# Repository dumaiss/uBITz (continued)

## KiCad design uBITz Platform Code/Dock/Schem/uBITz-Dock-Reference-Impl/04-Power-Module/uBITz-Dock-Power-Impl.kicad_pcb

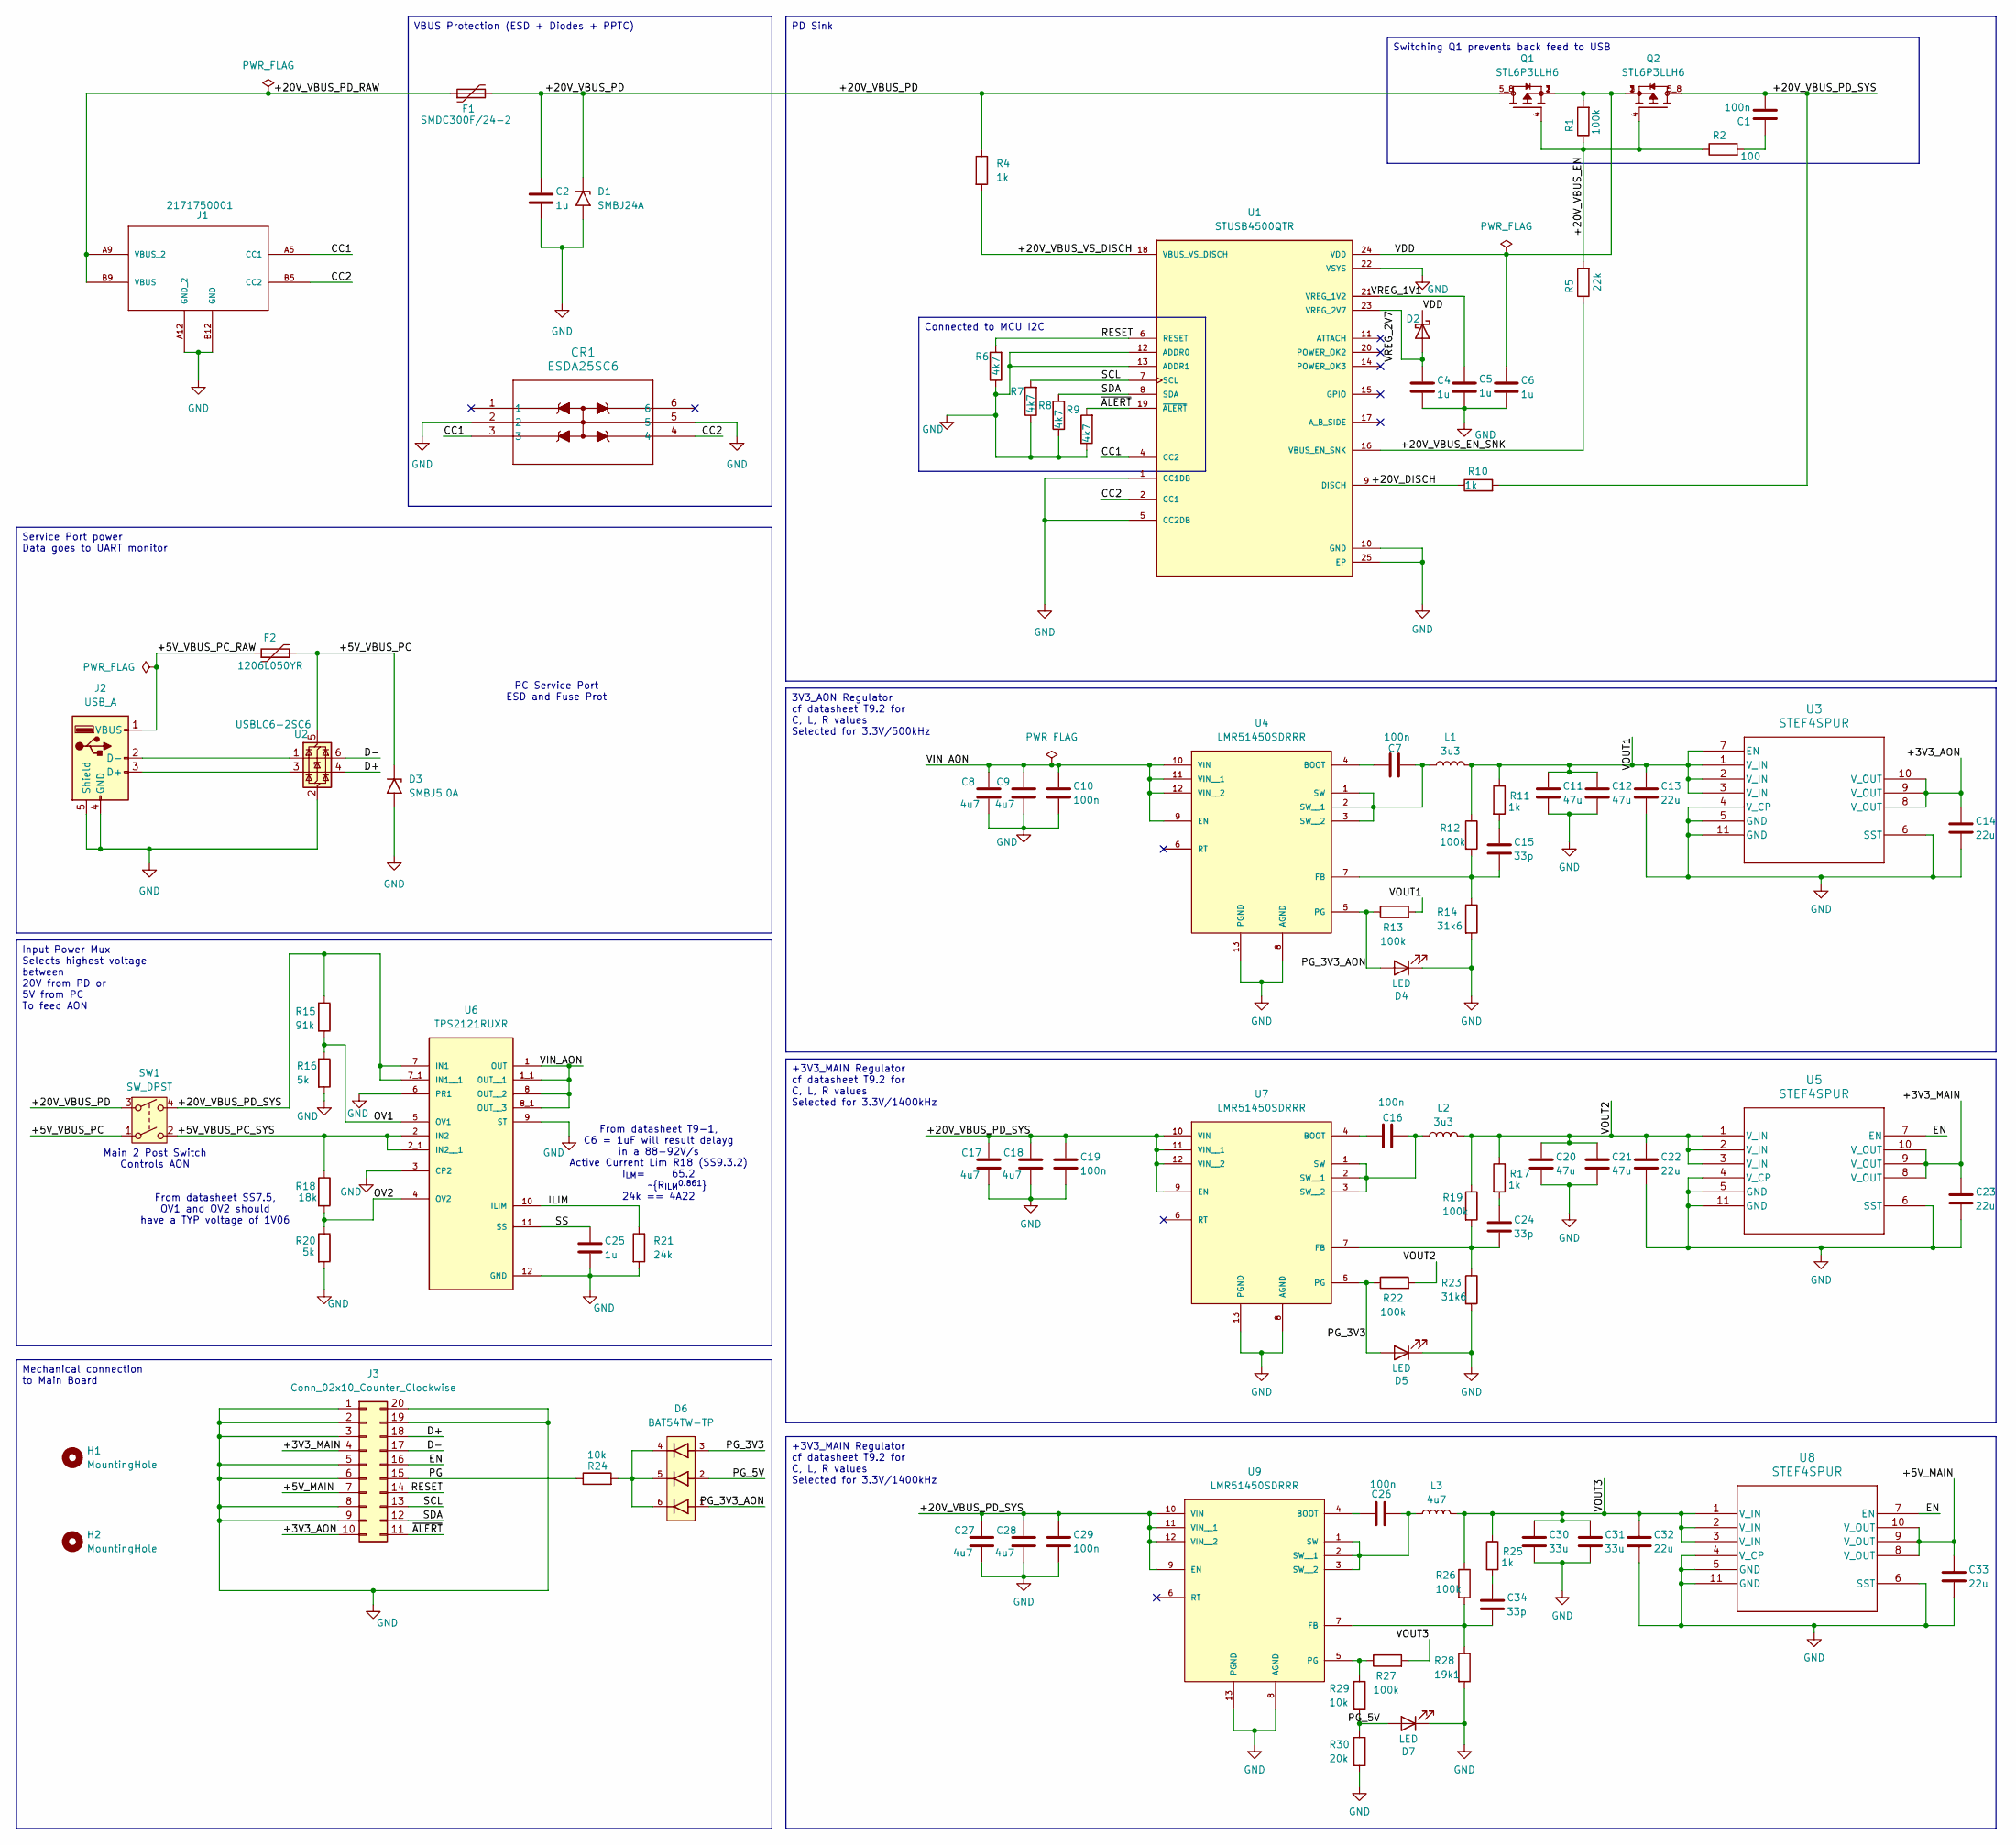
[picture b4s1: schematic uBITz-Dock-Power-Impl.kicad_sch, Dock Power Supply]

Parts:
C1, C7, C10, C16, C19, C26, C29: 100n; C_0603_1608Metric
C2: 1u; C_0402_1005Metric
C4, C5, C6, C25: 1u; C_0603_1608Metric
C8, C9, C17, C18, C27, C28: 4u7; C_0603_1608Metric
C11, C12, C20, C21: 47u; C_0603_1608Metric
C13, C14, C22, C23, C32, C33: 22u; C_0603_1608Metric
C15, C24, C34: 33p; C_0603_1608Metric
C30, C31: 33u; C_0603_1608Metric
CR1: ESDA25SC6; SOT23-6L_STM
D1: SMBJ24A; D_SMA_Handsoldering
D2: D_Schottky; D_SOD-323_HandSoldering
D3: SMBJ5.0A; D_SMB_Handsoldering
D4, D5, D7: LED; LED_0603_1608Metric
D6: BAT54TW-TP; SOP65P222X120-6N; PARTREV Rev.3
F1: SMDC300F/24-2; Fuse_2920_7451Metric_Pad2.10x5.45mm_HandSolder
F2: 1206L050YR; Fuse_1206_3216Metric
H1, H2: MountingHole; MountingHole_2.5mm
J1: 2171750001; 2171750001_MOL; MANUFACTURER_PART_NUMBER 2171750001
J2: USB_A; USB_A_Molex_67643_Horizontal
J3: Conn_02x10_Counter_Clockwise; PinHeader_2x10_P2.54mm_Vertical
L1, L2: 3u3; L_Bourns_SRP7028A_7.3x6.6mm; Part SRP7028A-3R3M
L3: 4u7; L_Bourns_SRP7028A_7.3x6.6mm
Q1, Q2: STL6P3LLH6; TRANS_STL6P3LLH6; PARTREV 4
R1, R12, R13, R19, R22, R26, R27: 100k; R_0603_1608Metric
R2: 100; R_0603_1608Metric
R4, R10, R11, R17, R25: 1k; R_0603_1608Metric
R5: 22k; R_0603_1608Metric
R6, R7, R8, R9: 4k7; R_0603_1608Metric
R14, R23: 31k6; R_0603_1608Metric
R15: 91k; R_0603_1608Metric
R16, R20: 5k; R_0603_1608Metric
R18: 18k; R_0603_1608Metric
R21: 24k; D_0603_1608Metric
R24, R29: 10k; R_0603_1608Metric
R28: 19k1; R_0603_1608Metric
R30: 20k; R_0603_1608Metric
SW1: SW_DPST; Molex_KK-254_AE-6410-04A_1x04_P2.54mm_Vertical; Part# 0022272041
U1: STUSB4500QTR; QFN50P400X400X90-25N; PARTREV 2
U2: USBLC6-2SC6; SOT-23-6
U3, U5, U8: STEF4SPUR; DFN_4SPUR_STM-L
U4, U7, U9: LMR51450SDRRR; CONV_LMR51450SDRRR; PARTREV December 2022
U6: TPS2121RUXR; IC_TPS2121RUXR

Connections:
/+3V3_AON: C14.1, J3.10, U3.8 (V_OUT), U3.9 (V_OUT), U3.10 (V_OUT)
/+3V3_MAIN: C23.1, J3.4, U5.8 (V_OUT), U5.9 (V_OUT), U5.10 (V_OUT)
/+5V_MAIN: C33.1, J3.7, U8.8 (V_OUT), U8.9 (V_OUT), U8.10 (V_OUT)
/+5V_VBUS_PC: D3.1 (A1), F2.2, SW1.1, U2.5 (VBUS)
/+5V_VBUS_PC_RAW: F2.1, J2.1 (VBUS)
/+5V_VBUS_PC_SYS: R18.1, SW1.2, U6.2 (IN2), U6.2_1 (IN2__1)
/+20V_DISCH: R10.1, U1.9 (DISCH)
/+20V_VBUS_EN: Q1.4, Q2.4, R1.1, R2.1, R5.2
/+20V_VBUS_EN_SNK: R5.1, U1.16 (VBUS_EN_SNK)
/+20V_VBUS_PD: C2.1, D1.1 (A1), F1.2, Q1.5_8, R4.1, SW1.3
/+20V_VBUS_PD_RAW: F1.1, J1.A9 (VBUS_2), J1.B9 (VBUS)
/+20V_VBUS_PD_SYS: C1.2, C17.1, C18.1, C19.1, C27.1, C28.1, C29.1, Q2.5_8, R10.2, R15.1, SW1.4, U6.7 (IN1), U6.7_1 (IN1__1), U7.9 (EN), U7.10 (VIN), U7.11 (VIN__1), U7.12 (VIN__2), U9.9 (EN), U9.10 (VIN), U9.11 (VIN__1), U9.12 (VIN__2)
/+20V_VBUS_VS_DISCH: R4.2, U1.18 (VBUS_VS_DISCH)
/CC1: CR1.3, J1.A5 (CC1), U1.4 (CC2)
/CC2: CR1.4, J1.B5 (CC2), U1.2 (CC1)
/D+: J3.18, U2.4 (I/O2)
/D-: J3.17, U2.6 (I/O1)
/EN: J3.16, U5.7 (EN), U8.7 (EN)
/ILIM: R21.1, U6.10 (ILIM)
/OV1: R15.2, R16.1, U6.5 (OV1)
/OV2: R18.2, R20.1, U6.4 (OV2)
/PG: J3.15, R24.1
/PG_3V3: D5.2 (A), D6.3, R22.1, U7.5 (PG)
/PG_3V3_AON: D4.2 (A), D6.1, R13.1, U4.5 (PG)
/PG_5V: D6.2, D7.2 (A), R29.2, R30.1
/RESET: J3.14, R6.2, U1.6 (RESET)
/SCL: J3.13, R7.2, U1.7 (SCL)
/SDA: J3.12, R8.2, U1.8 (SDA)
/SS: C25.1, U6.11 (SS)
/VDD: C6.1, D2.1 (K), Q1.1, Q1.2, Q1.3, Q2.1, Q2.2, Q2.3, R1.2, U1.24 (VDD)
/VIN_AON: C8.1, C9.1, C10.1, U4.9 (EN), U4.10 (VIN), U4.11 (VIN__1), U4.12 (VIN__2), U6.1 (OUT), U6.1_1 (OUT__1), U6.8 (OUT__2), U6.8_1 (OUT__3)
/VOUT1: C11.1, C12.1, C13.1, L1.2, R11.1, R12.1, R13.2, U3.1 (V_IN), U3.2 (V_IN), U3.3 (V_IN), U3.7 (EN)
/VOUT2: C20.1, C21.1, C22.1, L2.2, R17.1, R19.1, R22.2, U5.1 (V_IN), U5.2 (V_IN), U5.3 (V_IN)
/VOUT3: C30.1, C31.1, C32.1, L3.2, R25.1, R26.1, R27.2, U8.1 (V_IN), U8.2 (V_IN), U8.3 (V_IN)
/VREG_1V1: C5.1, U1.21 (VREG_1V2)
/VREG_2V7: C4.1, D2.2 (A), U1.23 (VREG_2V7)
/~ALERT: J3.11, R9.2, U1.19 (~ALERT)
GND: C2.2, C4.2, C5.2, C6.2, C8.2, C9.2, C10.2, C11.2, C12.2, C13.2, C14.2, C17.2, C18.2, C19.2, C20.2, C21.2, C22.2, C23.2, C25.2, C27.2, C28.2, C29.2, C30.2, C31.2, C32.2, C33.2, CR1.2, CR1.5, D1.2 (A2), D3.2 (A2), D4.1 (K), D5.1 (K), D7.1 (K), J1.A12 (GND_2), J1.B12 (GND), J2.4 (GND), J2.5 (Shield), J3.1, J3.2, J3.3, J3.5, J3.6, J3.8, J3.9, J3.19, J3.20, R6.1, R7.1, R8.1, R9.1, R14.2, R16.2, R20.2, R21.2, R23.2, R28.2, R30.2, U1.1 (CC1DB), U1.5 (CC2DB), U1.10 (GND), U1.12 (ADDR0), U1.13 (ADDR1), U1.22 (VSYS), U1.25 (EP), U2.2 (GND), U3.4 (V_CP), U3.5 (GND), U3.6 (SST), U3.11 (GND), U4.8 (AGND), U4.13 (PGND), U5.4 (V_CP), U5.5 (GND), U5.6 (SST), U5.11 (GND), U6.3 (CP2), U6.6 (PR1), U6.9 (ST), U6.12 (GND), U7.8 (AGND), U7.13 (PGND), U8.4 (V_CP), U8.5 (GND), U8.6 (SST), U8.11 (GND), U9.8 (AGND), U9.13 (PGND)
unnamed: C1.1, R2.2
unnamed: C15.1, R11.2
unnamed: C24.1, R17.2
unnamed: C34.1, R25.2
unnamed: D6.4, D6.5, D6.6, R24.2
unnamed: J2.3 (D+), U2.3 (I/O2)
unnamed: J2.2 (D-), U2.1 (I/O1)
unnamed: C7.2, U4.4 (BOOT)
unnamed: C15.2, R12.2, R14.1, U4.7 (FB)
unnamed: C7.1, L1.1, U4.1 (SW), U4.2 (SW__1), U4.3 (SW__2)
unnamed: C16.2, U7.4 (BOOT)
unnamed: C24.2, R19.2, R23.1, U7.7 (FB)
unnamed: C16.1, L2.1, U7.1 (SW), U7.2 (SW__1), U7.3 (SW__2)
unnamed: C26.2, U9.4 (BOOT)
unnamed: C34.2, R26.2, R28.1, U9.7 (FB)
unnamed: R27.1, R29.1, U9.5 (PG)
unnamed: C26.1, L3.1, U9.1 (SW), U9.2 (SW__1), U9.3 (SW__2)

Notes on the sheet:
Active Current Lim R18 (SS9.3.2) I_{LM}= 65.2 ~{R_{ILM}^{0.861}} 24k == 4A22
Main 2 Post Switch Controls AON
From datasheet T9-1, C6 = 1uF will result delayg in a 88-92V/s
From datasheet SS7.5, OV1 and OV2 should have a TYP voltage of 1V06
PC Service Port ESD and Fuse Prot
Service Port power Data goes to UART monitor
3V3_AON Regulator cf datasheet T9.2 for C, L, R values Selected for 3.3V/500kHz
Switching Q1 prevents back feed to USB
Input Power Mux Selects highest voltage between 20V from PD or 5V from PC To feed AON
+3V3_MAIN Regulator cf datasheet T9.2 for C, L, R values Selected for 3.3V/1400kHz
Mechanical connection to Main Board
PD Sink
Connected to MCU I2C
VBUS Protection (ESD + Diodes + PPTC)

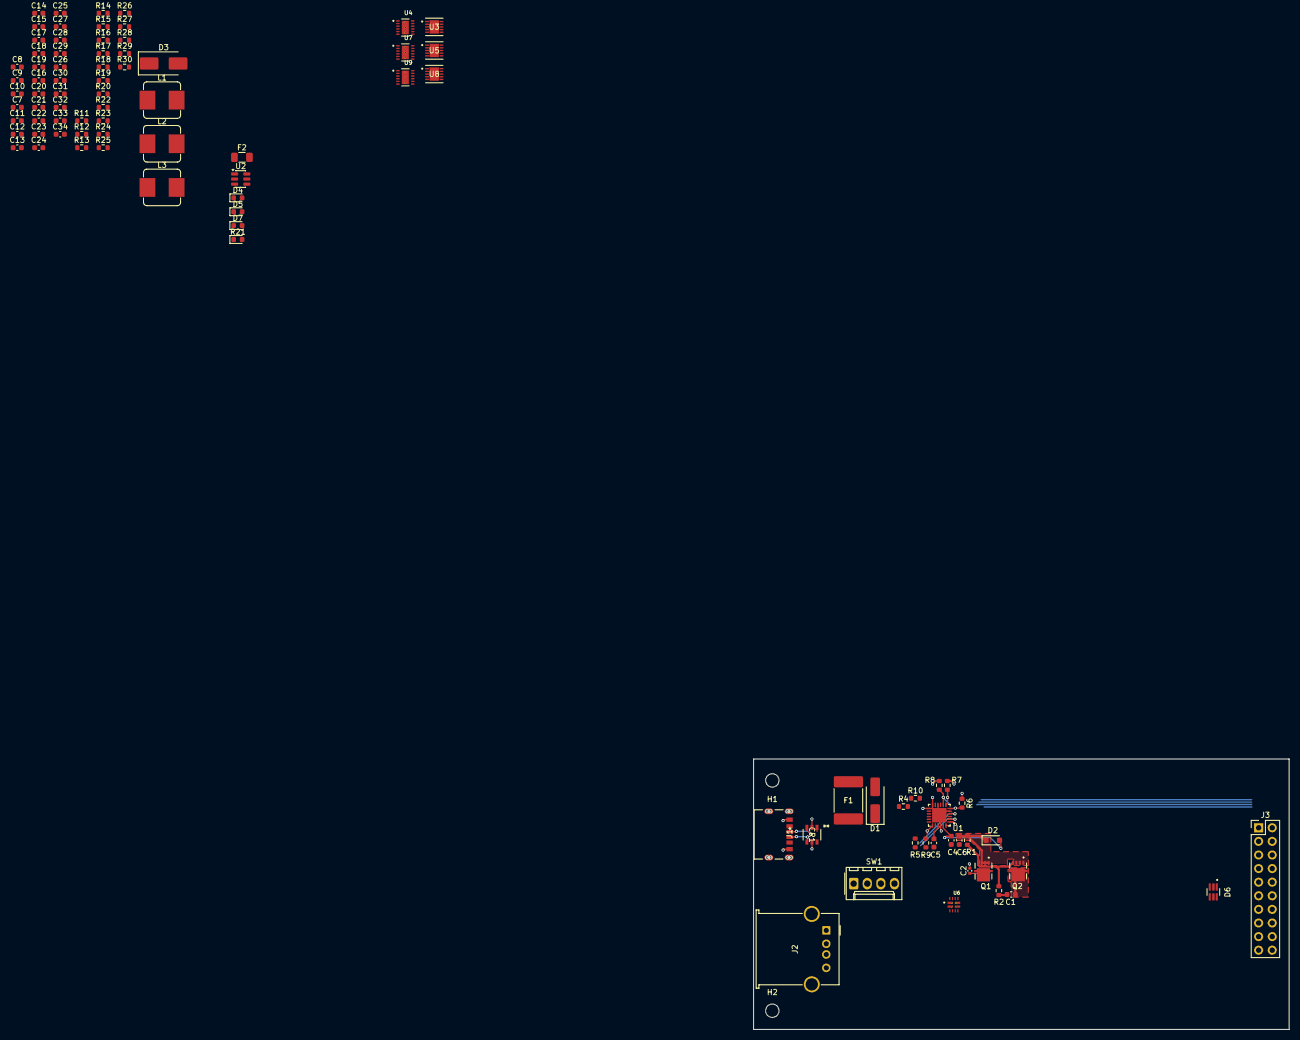
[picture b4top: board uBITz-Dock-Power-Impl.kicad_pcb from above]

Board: 4 copper layers, 100.0 x 50.5 mm, 92 parts (0 on the bottom side), 55 nets.

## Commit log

2025-10-31 Add Solderpad Hardware License v2.1
    Added Solderpad Hardware License v2.1 to the project.
2025-10-31 Improve README.md formatting
    Added a blank line for better readability.
2025-10-31 Add μBITz trademarks policy document
    This document outlines the trademarks policy for μBITz, including acceptable and unacceptable uses of the trademarks, ownership details, and logo usage rules.
2025-10-31 Logo
    Added Logo
2025-11-18 DESKTOP-2HS1J3F 2025-11-18:13:38:34
2025-11-18 DESKTOP-2HS1J3F 2025-11-18:13:39:20
2025-11-18 DESKTOP-2HS1J3F 2025-11-18:13:48:15
2025-11-18 DESKTOP-2HS1J3F 2025-11-18:14:55:22
2025-11-18 DESKTOP-2HS1J3F 2025-11-18:15:32:24
2025-11-18 DESKTOP-2HS1J3F 2025-11-18:16:8:13
2025-11-19 unused files
2025-11-21 First commit of the Dock module before interrupt handling
2025-11-21 Added utility to generate utilization report
2025-11-21 Update CMakeLists.txt for FPGA synthesis and routing targets
2025-11-21 ignored more stuff
2025-11-21 DESKTOP-2HS1J3F 2025-11-21:14:50:57
2025-11-21 fedora 2025-11-21:15:38:0
2025-11-21 updates for the intterupts
2025-11-21 feat: add irq router module and tests
2025-11-21 refactor: rename address decoder top
2025-11-21 refactor: rename addr_decoder submodules
2025-11-21 chore: align addr_decoder PCF and testbench names
2025-11-22 feat: handle mode-2 vector fetch
2025-11-22 moved the test description
2025-11-22 docs: document addr_decoder wiring
2025-11-22 docs: document addr decoder submodules
2025-11-22 docs: document irq router flow
2025-11-22 chore: drop unused legacy irq module
2025-11-22 chore: remove legacy irq testbench
2025-11-22 update to doc
2025-11-22 docs: update agent guidelines for build/tests
2025-11-22 Added new documentation files for DECODER_CONFIGURATION and SIGNALS.
2025-11-22 Small update to README.md and addition of DECODER_CONFIGURATION.md and SIGNALS.md
2025-11-22 docs: remind to keep docs in sync
2025-11-22 more doc
2025-11-24 Added implementation notes and parallel profile
    Added implementation notes and parallel profile
2025-11-24 DESKTOP-2HS1J3F 2025-11-24:13:17:24
2025-11-24 DESKTOP-2HS1J3F 2025-11-24:13:26:38
2025-11-24 DESKTOP-2HS1J3F 2025-11-24:14:16:52
2025-11-24 DESKTOP-2HS1J3F 2025-11-24:14:47:7
2025-11-24 DESKTOP-2HS1J3F 2025-11-24:16:15:36
2025-11-24 DESKTOP-2HS1J3F 2025-11-24:18:1:47
2025-11-24 Move all HDL source files into HDL subdirectory
2025-11-27 274bitz_dock_power_system_architecture_2025_11_26 added
2025-11-27 Update README.md
    Typo
2025-11-28 Digital Subsystem architecture
    Digital Subsystem architecture
2025-11-29 Updated the configuration mechanism to be able to configure both IRQ Router and Address Decoder with a single cfg bus and unified the whole module in TOP
2025-11-29 correcting issues with multiple assignments in synthesis
    correcting issues with multiple assignments in synthesis
2025-11-29 added AI Assisted Development guidelines and policies
2025-11-29 DESKTOP-2HS1J3F 2025-11-29:15:11:53
2025-11-29 clean up some changes that were not supposed to be committed
2025-11-29 ignore some stuff
2025-11-30 Package for iCE40 HK FPGA
2025-11-30 Git Ignore build directory
2025-11-30 Fix issue with test suite
2025-12-24 Host and Dock first commit along with all the symbols, datasheets and footprints
2025-12-24 Fixed left overs from the RAM/ROM_CS to MEM0/MEM1_CS rename
2025-12-24 Updated spec to reassign pins for GPIOs to provide clock distribution from host to system and from dock to system
2025-12-24 Reserved DMA pins
2025-12-24 Engineering Diary
2025-12-24 Git Ignore maintenance
2025-12-29 DESKTOP-2HS1J3F 2025-12-28:23:12:45
2025-12-29 Removed the Serial Profile and first commit of the a Host
2025-12-30 Fixes to specs
2025-12-30 Change odd/even for A/B to match the symbol diagram
2025-12-30 Reverted A and B
2026-01-03 Committing the first fully completed version of the Z80 based host
2026-01-03 Gitignore Cleanup
2026-01-03 Added the ability to tri-state the MEM0_CS and MEM1_CS signals to allow the Dock to take over memory type selection based on addresses
2026-01-03 Added 6309 based host Cleaned up pins assignent on edge connector Made /READY signal time bound
2026-01-03 EngineeringDiary added
2026-01-04 Modified Pinout for easier layout Moved processing of MEM0_CS and MEM1_CS to Dock, no longer needed on Host
2026-01-04 Rearranged the edge connector pins
2026-01-04 Fixed the arrows
2026-01-04 Updated spec for memory address decoding.
2026-01-04 Fixed a couple of inconsistencies with memory decoding
2026-01-04 Fixed some ambiguities in the address decoding Added the changes to prepare for bus mastering fixed some inconsistencies in memory address decoding
2026-01-04 Updated the Dock signaling voltage section and buffering
2026-01-04 Engineering diary for today
2026-01-04 Forgot the pin names
2026-01-05 Added a Z80 host without mapper nor programmer Moved 6309 directory
    Added instructions about floating pins
2026-01-05 missing updates
2026-01-05 Corrected Bus width (19-bits from 20-bits) and corrected mapper wiring, which needs to be able to re-write bits A13-A15
2026-01-05 Corrected for bus width (20 -> 19) and allowd mapper to rewrite bits A13-A15 of the address bus (become PA13-PA15)
2026-01-05 Beautify board and schematic Added PDF
2026-01-05 Removed transceivers from Z80 host with the mapper and cleaned up schematics
2026-01-05 Added Programmer board
2026-01-07 DESKTOP-2HS1J3F 2026-1-7:12:1:37
2026-01-07 Fixed a bad commit reverting change
    Fixed a bad commit reverting change
2026-01-09 Adding the first Bank ref impl
